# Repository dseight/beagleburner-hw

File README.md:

# BeagleBurner HW

Simple BeagleBone Black cape for [BeagleBurner] project. Designed in KiCad 10.

## License

Licensed under [CERN Open Hardware Licence Version 2 - Permissive](LICENSE).

[BeagleBurner]: https://github.com/dseight/beagleburner

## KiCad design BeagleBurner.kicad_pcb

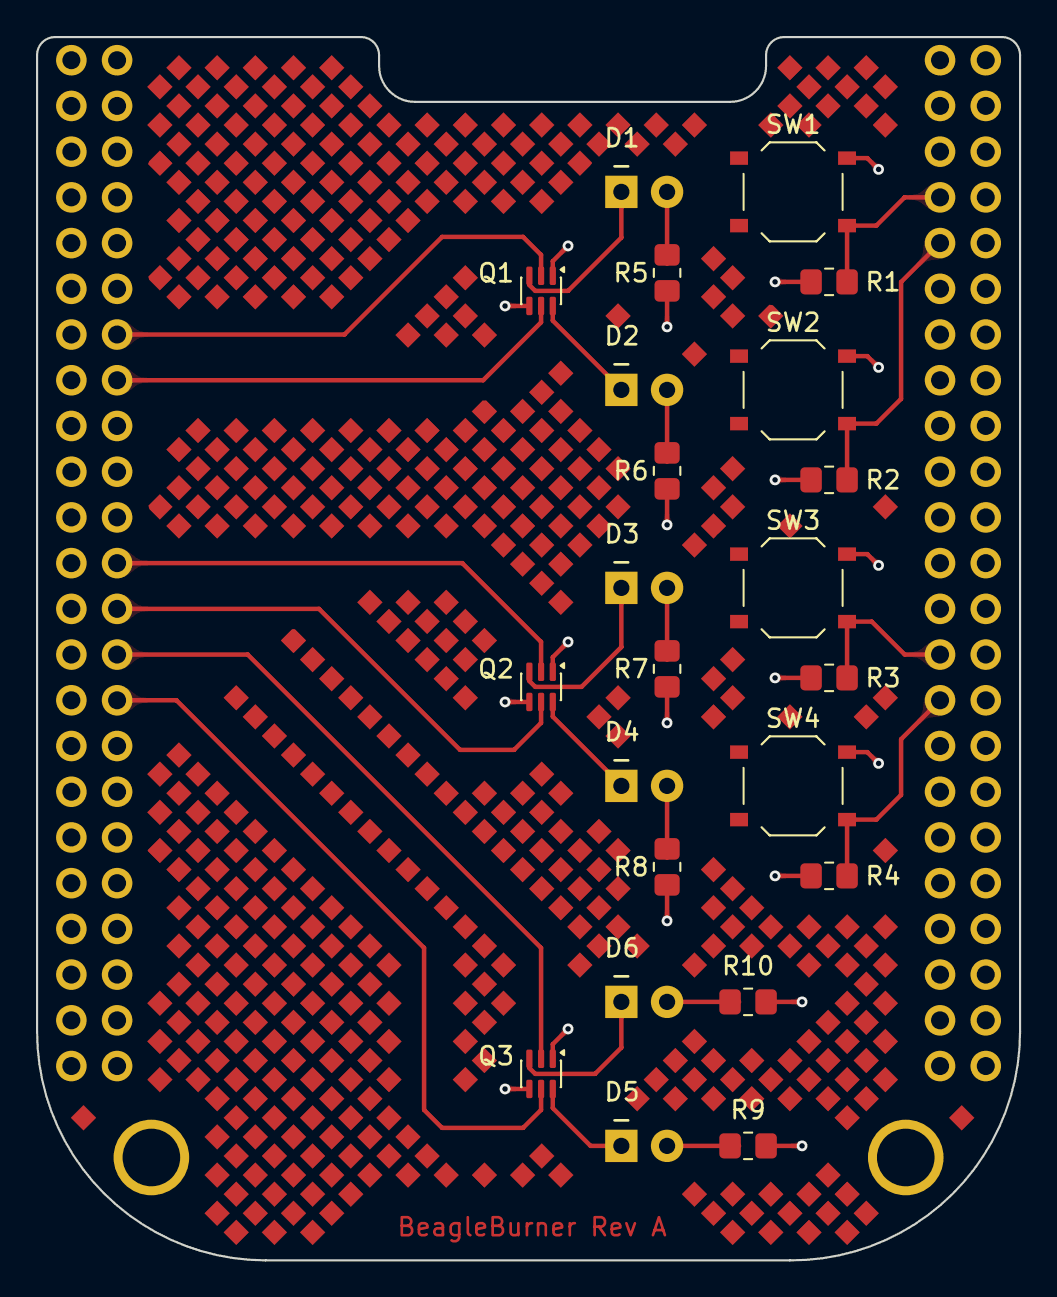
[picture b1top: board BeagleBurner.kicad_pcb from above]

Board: 4 copper layers, 54.6 x 68.0 mm, 24 parts (0 on the bottom side), 24 nets.

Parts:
A1: BeagleBone Black; BeagleBoneBlack
D1, D2, D3, D4: LED ORANGE; LED_D3.0mm
D5: LED RED; LED_D3.0mm
D6: LED GREEN; LED_D3.0mm
Q1, Q2, Q3: DDC114EU-7-F; SOT-363_SC-70-6
R1, R2, R3, R4: 10K; R_0805_2012Metric_Pad1.20x1.40mm_HandSolder
R5, R6, R7, R8, R9, R10: 240R; R_0805_2012Metric_Pad1.20x1.40mm_HandSolder
SW1, SW2, SW3, SW4: TS-1187A-B-A-B; SW_Push_1P1T_XKB_TS-1187A

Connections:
+3V3: A1.49 (DC_3.3V), A1.50 (DC_3.3V), R1.1, R2.1, R3.1, R4.1, R5.1, R6.1, R7.1, R8.1, R9.1, R10.1
/BTN1: A1.7 (gpio2_2), R1.2, SW1.2
/BTN2: A1.9 (gpio2_5), R2.2, SW2.2
/BTN3: A1.27 (gpio2_22), R3.2, SW3.2
/BTN4: A1.29 (gpio2_23), R4.2, SW4.2
/LED1: A1.62 (gpio1_19), Q1.5 (B2)
/LED2: A1.60 (gpio1_18), Q1.2 (B1)
/LED3: A1.72 (gpio0_14), Q2.5 (B2)
/LED4: A1.70 (gpio0_15), Q2.2 (B1)
/LED5: A1.74 (gpio3_17), Q3.2 (B1)
/LED6: A1.76 (gpio3_16), Q3.5 (B2)
GND: A1.1 (GND), A1.2 (GND), A1.47 (GND), A1.48 (GND), A1.89 (GND), A1.90 (GND), A1.91 (GND), A1.92 (GND), Q1.1 (E1), Q1.4 (E2), Q2.1 (E1), Q2.4 (E2), Q3.1 (E1), Q3.4 (E2), SW1.1, SW2.1, SW3.1, SW4.1
unnamed: D1.2 (A), R5.2
unnamed: D1.1 (K), Q1.3 (C2)
unnamed: D2.2 (A), R6.2
unnamed: D2.1 (K), Q1.6 (C1)
unnamed: D3.2 (A), R7.2
unnamed: D3.1 (K), Q2.3 (C2)
unnamed: D4.2 (A), R8.2
unnamed: D4.1 (K), Q2.6 (C1)
unnamed: D5.2 (A), R9.2
unnamed: D5.1 (K), Q3.6 (C1)
unnamed: D6.2 (A), R10.2
unnamed: D6.1 (K), Q3.3 (C2)
